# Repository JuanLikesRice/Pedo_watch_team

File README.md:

# Pedo_watch_team
Final for Elec327 code for MSP430

Website explaining our Design: https://olr148.wixsite.com/pedowatchteam/

DataSHeets for the pedometer sensor:
https://download.mikroe.com/documents/datasheets/KX126-1063.pdf
https://kionixfs.azureedge.net/en/document/AN073-Getting-Started-with-Pedometer.pdf

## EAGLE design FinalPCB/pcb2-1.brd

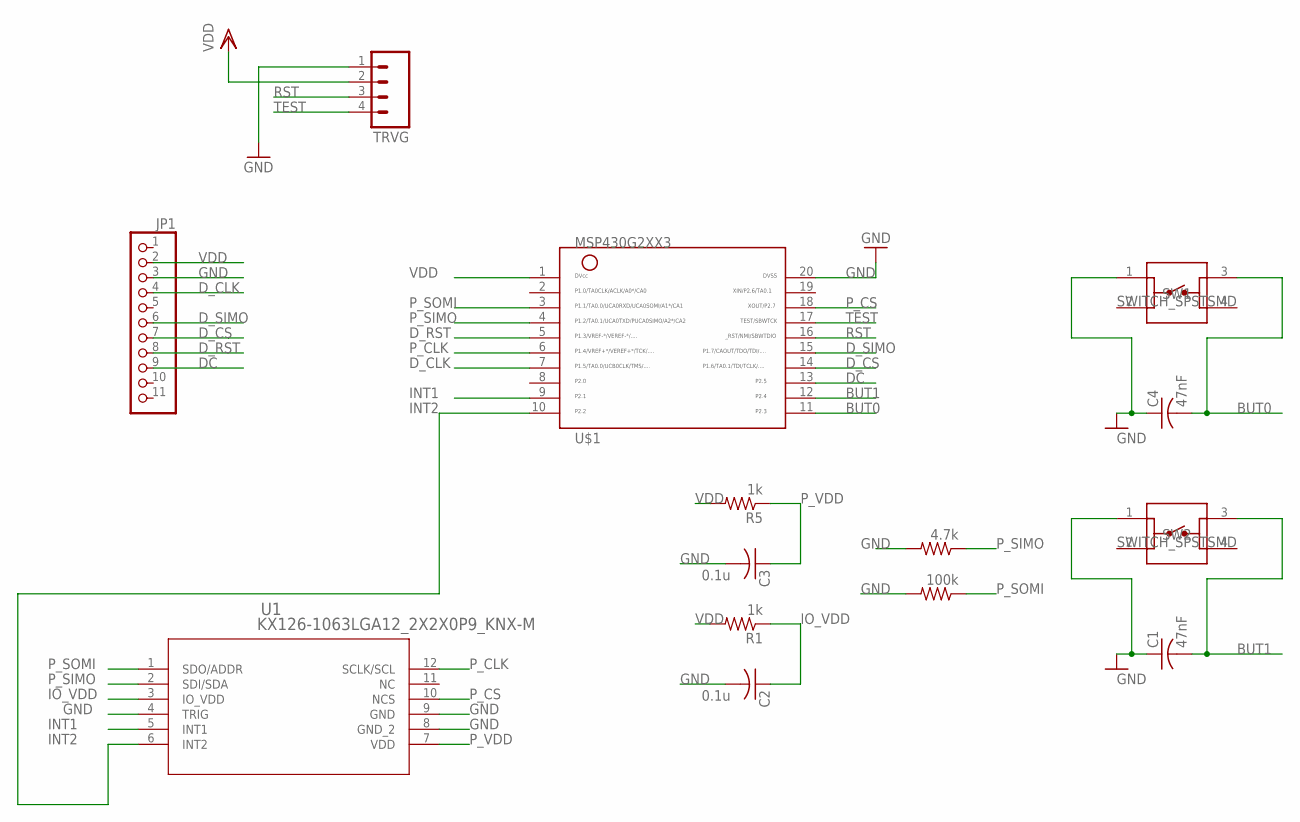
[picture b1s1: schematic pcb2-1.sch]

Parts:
C1, C4: 47nF; C0603
C2, C3: 0.1u; C0603
JP1: HEADER-1X11; 1X11_ROUND
R1, R5: 1k; R0402
R2: 100k; R0402
R3: 4.7k; R0402
SW1, SW2: SWITCH_SPSTSMD; SW_1571563-4
TRVG: M04LOCK; 1X04_LOCK
U1: KX126-1063LGA12_2X2X0P9_KNX-M; LGA12_2X2X0P9_KNX-M
U$1: MSP430G2XX3TSSOP; PW20

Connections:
BUT0: C4.2, SW1.3, U$1.11
BUT1: C1.2, SW2.3, U$1.12
DC: JP1.9, U$1.13
D_CLK: JP1.4, U$1.7
D_CS: JP1.7, U$1.14
D_RST: JP1.8, U$1.5
D_SIMO: JP1.6, U$1.15
GND: C1.1, C2.2, C3.2, C4.1, JP1.3, R2.2, R3.2, SW1.1, SW2.1, TRVG.1, U1.4 (TRIG), U1.8 (GND_2), U1.9 (GND), U$1.20
INT1: U1.5 (INT1), U$1.9
INT2: U1.6 (INT2), U$1.10
IO_VDD: C2.1, R1.1, U1.3 (IO_VDD)
P_CLK: U1.12 (SCLK/SCL), U$1.6
P_CS: U1.10 (NCS), U$1.18
P_SIMO: R3.1, U1.2 (SDI/SDA), U$1.4
P_SOMI: R2.1, U1.1 (SDO/ADDR), U$1.3
P_VDD: C3.1, R5.1, U1.7 (VDD)
RST: TRVG.3, U$1.16
TEST: TRVG.4, U$1.17
VDD: JP1.2, R1.2, R5.2, TRVG.2, U$1.1

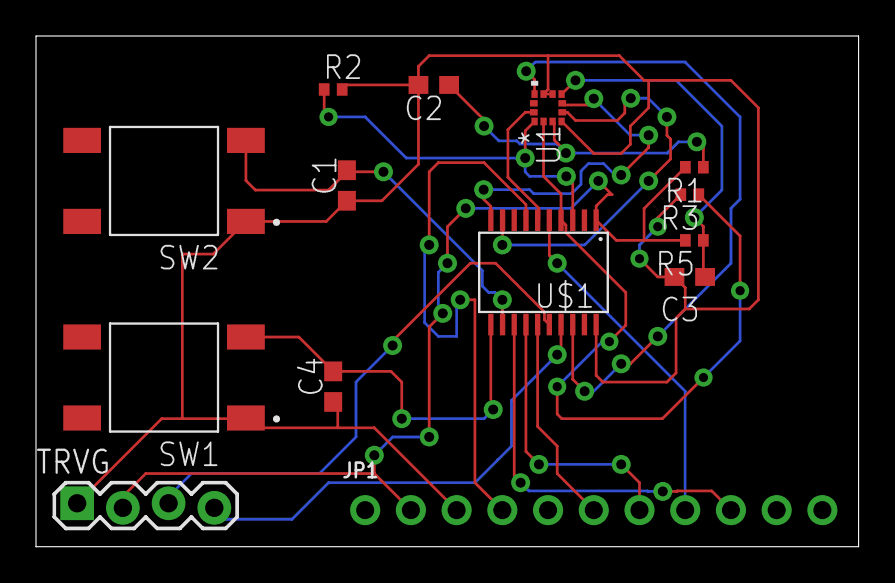
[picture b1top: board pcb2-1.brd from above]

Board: 2 copper layers, 45.7 x 28.4 mm, 14 parts (0 on the bottom side), 19 nets.

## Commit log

2022-04-11 mase main.c
2022-04-11 added PCB files
2022-04-11 added CAM files for final1
2022-04-13 update the read and write buffers
2022-04-13 Son s display
2022-04-13 more updates for backup!
2022-04-13 working code fopr read a nd write!
2022-04-13 simple code for reqad and write1
2022-04-13 reads steps but very bad
2022-04-13 reads steps but badly
2022-04-14 added
2022-04-14 so close my love
2022-04-15 alm,ost there pt2
2022-04-15 final2
2022-04-15 reads address 0x0E, basically steps! with a catch
    Can read pedo_stp_L (0x0E), the issue is that when it you would want to read pedo_stp_L (0x0F), you for some reason will always read zero when you read pedo_stp_L???? For the pedometer, the code for 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
2022-04-15 readme for datasheets
2022-04-18 now with interupt
2022-04-18 working shi
2022-04-18 2nd pcb files
2022-04-18 working code
2022-04-25 works but cooler
2022-04-25 Updated display code
2022-04-25 finalPCB
2022-04-25 FINAL PCB files
2022-04-29 intergrating
2022-04-30 need comments
2022-05-01 updated codes
2022-05-02 Comments for Pedometer
2022-05-04 FINAL PCB - Schematic and Board files
2022-05-05 Final working
2022-05-05 comments
2022-05-05 Rename main.c to Old_file_not_part_of_submission.c

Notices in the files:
parts and their libraries:
COPYRIGHT: Copyright (C) 2021 Ultra Librarian. All rights reserved.
